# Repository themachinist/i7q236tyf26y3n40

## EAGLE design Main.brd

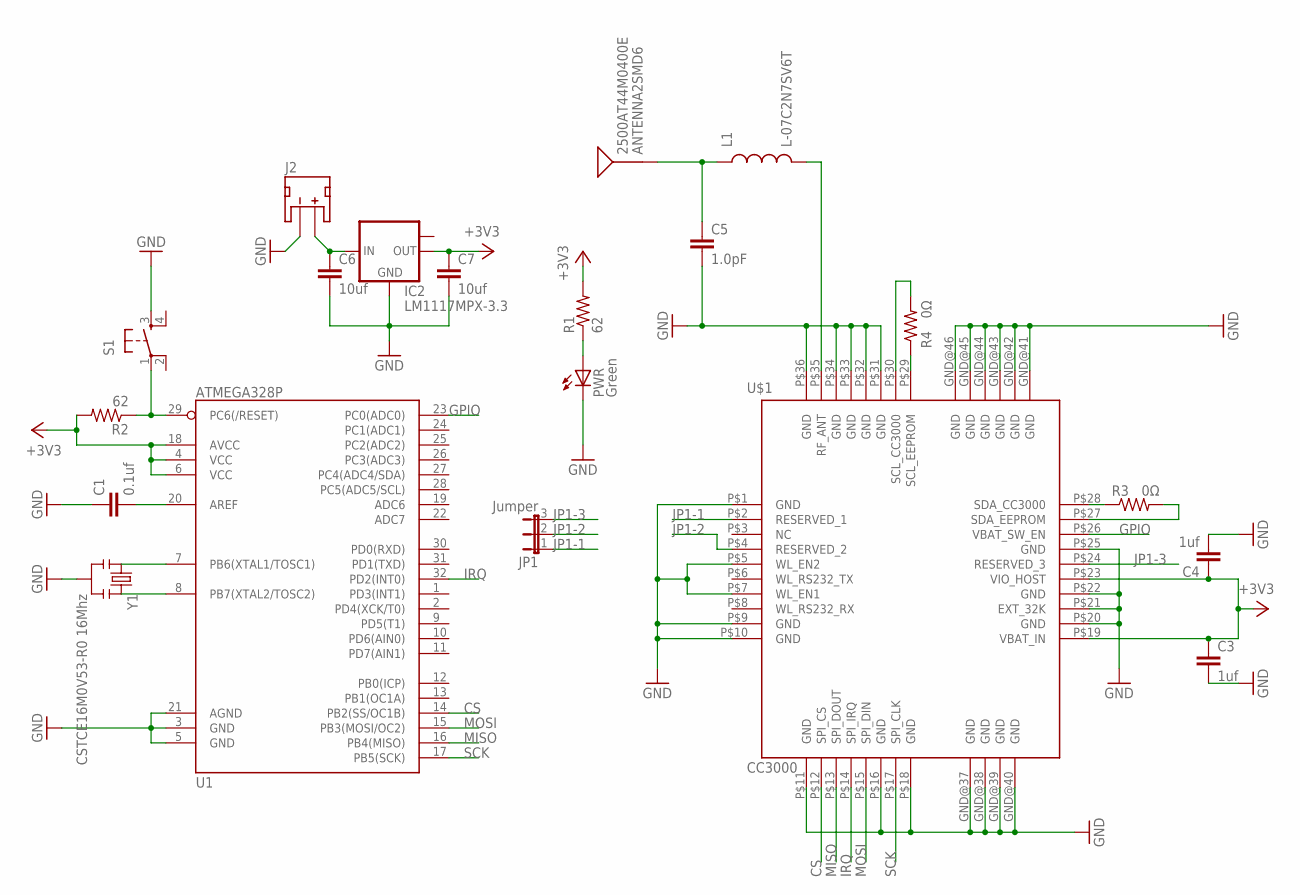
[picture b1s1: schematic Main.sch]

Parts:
2500AT44M0400E: ANTENNA2SMD6; ANTENNA-CHIP6
C1: 0.1uf; C0805
C3, C4: 1uf; C0805
C5: 1.0pF; 0603-CAP
C6, C7: 10uf; C0805
IC2: LM1117MPX-3.3; SOT223
J2: JST_2MM_MALE; JST-2-SMD
JP1: Jumper; JP2
L1: L-07C2N7SV6T; C0402
PWR: Green; CHIPLED_1206
R1, R2: 62; R0805
R3, R4: 0Ω; 0603-RES
S1: TAC_SWITCHSMD; TACTILE_SWITCH_SMD
U1: ATMEGA328P; TQFP32-08
U$1: CC3000; QFN-46_CC3000
Y1: CSTCE16M0V53-R0 16Mhz; RESONATOR-SMD

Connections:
+3V3: C3.1, C4.1, R1.2, R2.2, U1.4 (VCC), U1.6 (VCC), U1.18 (AVCC), U$1.P$19 (VBAT_IN), U$1.P$23 (VIO_HOST)
CS: U1.14 (PB2(SS/OC1B)), U$1.P$12 (SPI_CS)
GND: C1.1, C3.2, C4.2, C5.2, C6.2, C7.2, IC2.1 (GND), J2.1 (-), PWR.C, S1.3, U1.3 (GND), U1.5 (GND), U1.21 (AGND), U$1.GND@37 (GND), U$1.GND@40 (GND), U$1.GND@41 (GND), U$1.GND@42 (GND), U$1.GND@43 (GND), U$1.GND@44 (GND), U$1.GND@45 (GND), U$1.GND@46 (GND), U$1.P$1 (GND), U$1.P$5 (WL_EN2), U$1.P$7 (WL_EN1), U$1.P$10 (GND), U$1.P$11 (GND), U$1.P$16 (GND), U$1.P$20 (GND), U$1.P$21 (EXT_32K), U$1.P$22 (GND), U$1.P$25 (GND), U$1.P$31 (GND), U$1.P$32 (GND), U$1.P$33 (GND), U$1.P$34 (GND), U$1.P$36 (GND), Y1.2
GPIO: U1.23 (PC0(ADC0)), U$1.P$26 (VBAT_SW_EN)
IN: C6.1, IC2.3 (IN), J2.2 (+)
IRQ: U1.32 (PD2(INT0)), U$1.P$14 (SPI_IRQ)
JP1-1: JP1.1, U$1.P$2 (RESERVED_1)
JP1-2: JP1.2, U$1.P$4 (RESERVED_2)
JP1-3: JP1.3, U$1.P$24 (RESERVED_3)
MISO: U1.16 (PB4(MISO))
MOSI: U1.15 (PB3(MOSI/OC2)), U$1.P$15 (SPI_DIN)
unnamed: PWR.A, R1.1
unnamed: U1.8 (PB7(XTAL2/TOSC2)), Y1.3
unnamed: U1.7 (PB6(XTAL1/TOSC1)), Y1.1
unnamed: C1.2, U1.20 (AREF)
unnamed: L1.2, U$1.P$35 (RF_ANT)
unnamed: R3.2, U$1.P$27 (SDA_EEPROM)
unnamed: R3.1, U$1.P$28 (SDA_CC3000)
unnamed: R4.1, U$1.P$29 (SCL_EEPROM)
unnamed: R4.2, U$1.P$30 (SCL_CC3000)
unnamed: 2500AT44M0400E.1, C5.1, L1.1
OUT: C7.1, IC2.2 (OUT)
RESET: R2.1, S1.1, U1.29 (PC6(/RESET))
SCK: U1.17 (PB5(SCK)), U$1.P$17 (SPI_CLK)

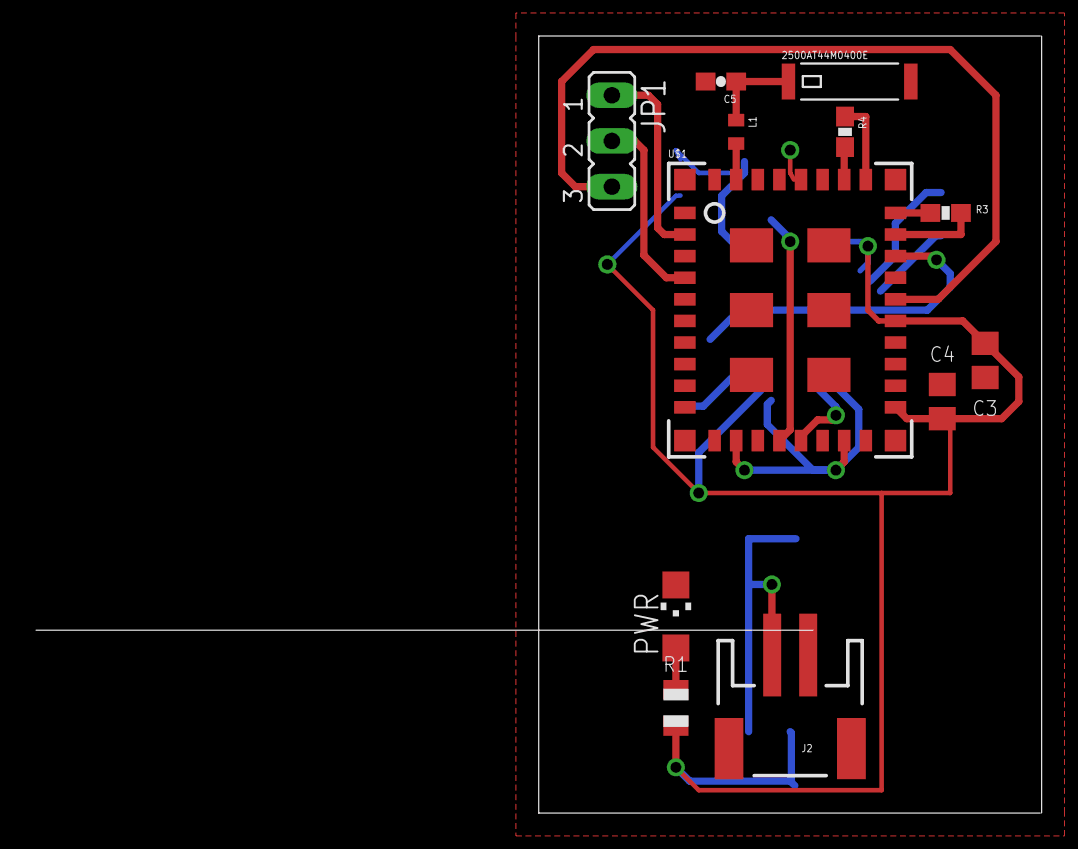
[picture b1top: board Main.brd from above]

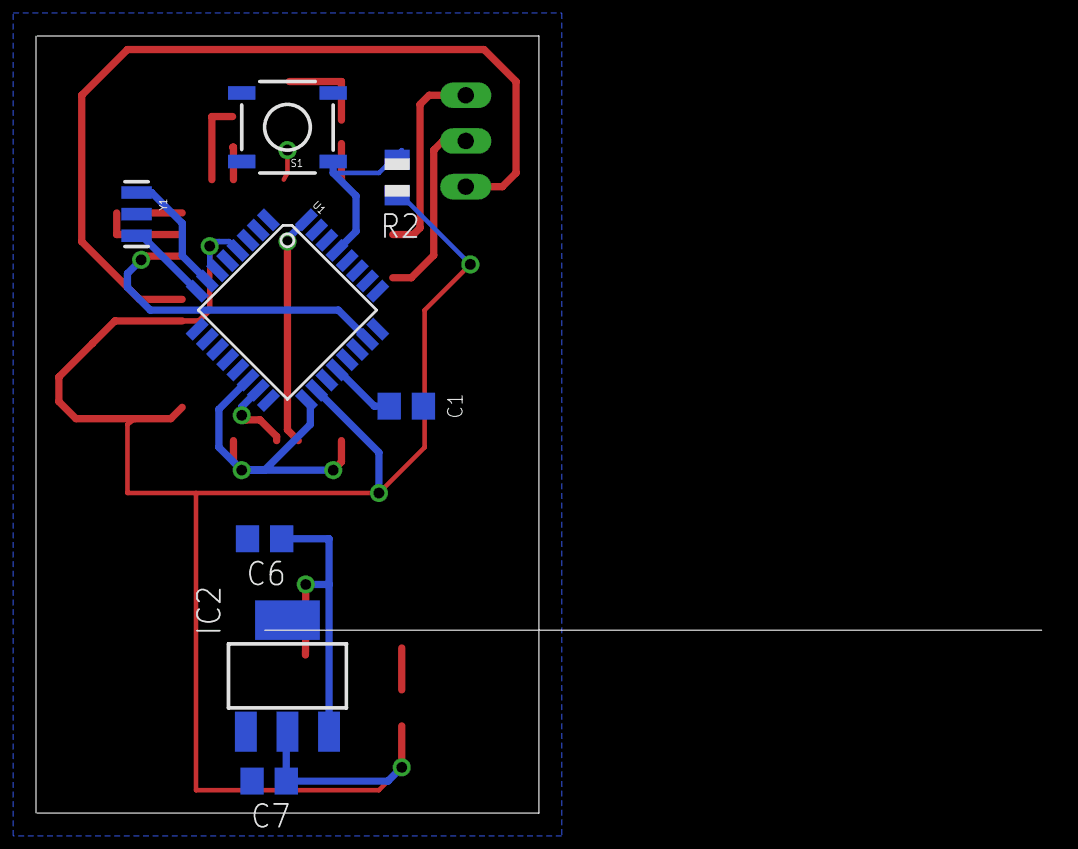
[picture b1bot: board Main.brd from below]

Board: 2 copper layers, 55.9 x 43.2 mm, 20 parts (8 on the bottom side), 23 nets.

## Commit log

2014-07-29 Create firm.ino
    read output from calipers

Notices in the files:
parts and their libraries:
SparkFun-RF: Licensing: CC v3.0 Share-Alike You are welcome to use this library for commercial purposes.
